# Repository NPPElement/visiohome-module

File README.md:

# visiohome-module

Open Source Hardware VHM ESP32 development board designed with KiCAD, with additional LiPo charger and battery.

## License
* Hardware is released under Apache 2.0 License
* Software is released under GPL3 License

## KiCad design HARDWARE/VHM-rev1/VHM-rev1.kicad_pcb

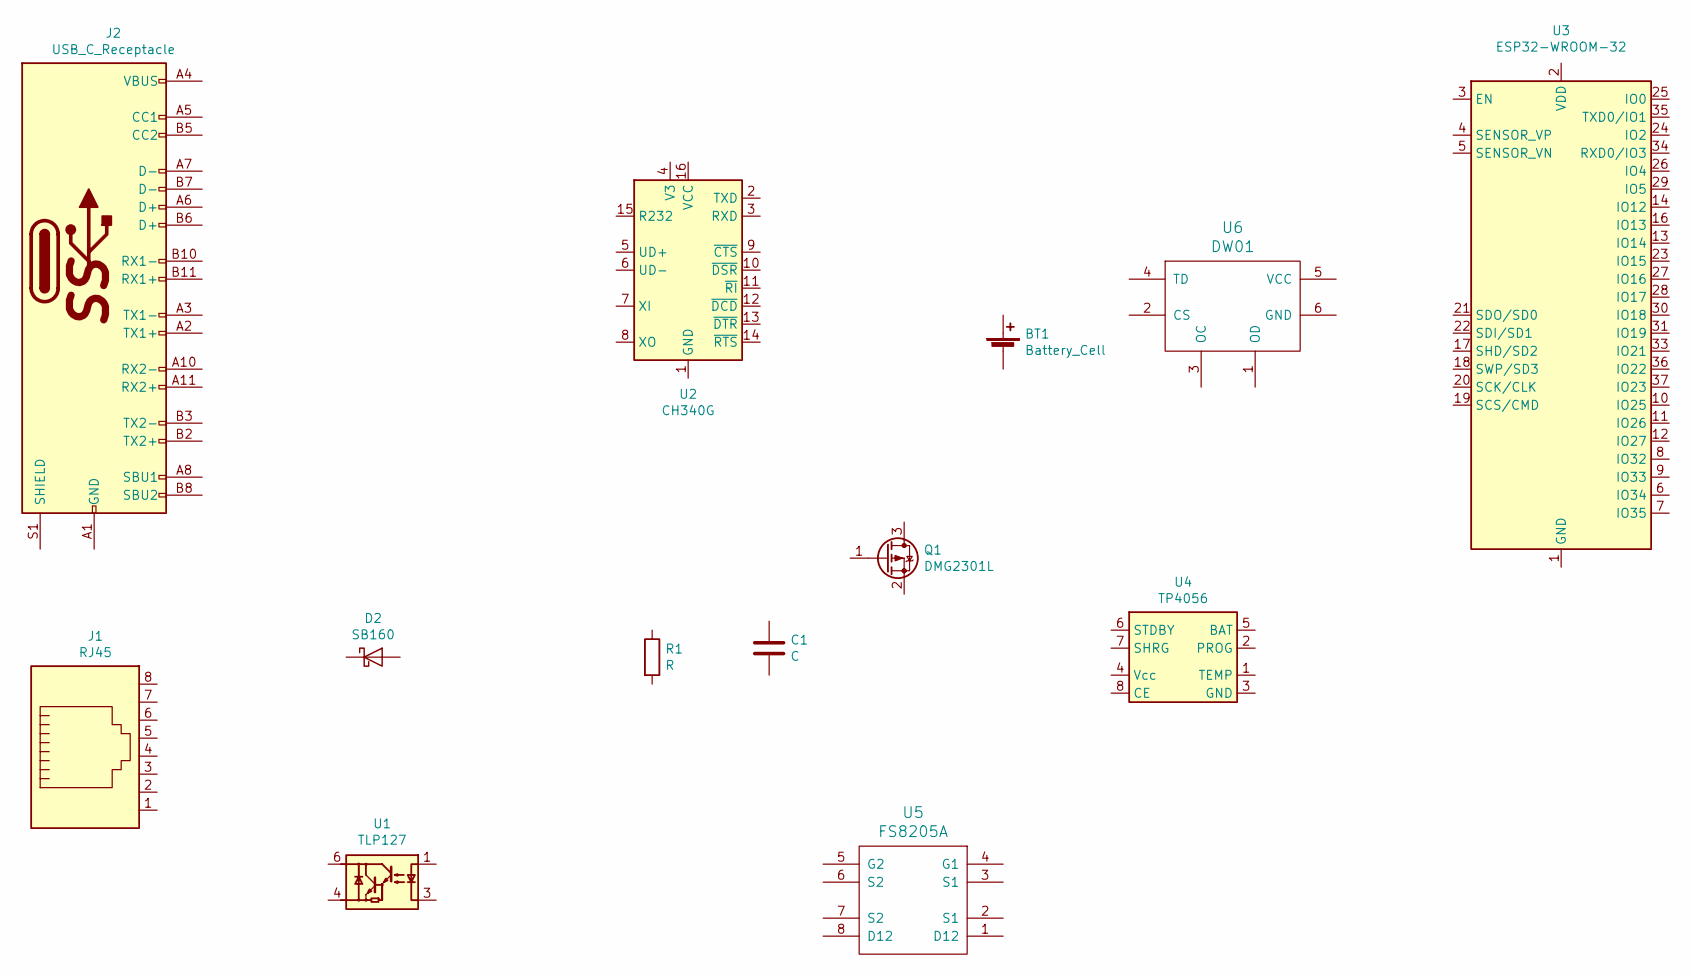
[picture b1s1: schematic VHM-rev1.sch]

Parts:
BT1: Battery_Cell; Keystone_1042_1x18650
C1: C; C_0603
D2: SB160; D_SMA
J1: RJ45; RJ45_8
J2: USB_C_Receptacle; USB_C_Plug_Molex_105444
Q1: DMG2301L; SOT-23
R1: R; R_0603
U1: TLP127; MFSOP6-4_4.4x3.6mm_Pitch1.27mm
U2: CH340G; SO-16-N
U3: ESP32-WROOM-32; ESP32-WROOM
U4: TP4056; TP4056_SOP-8-PP
U5: FS8205A; TSSOP-8_4.4x3mm_Pitch0.65mm
U6: DW01; SOT-23-6_Handsoldering

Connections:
unnamed: J2.A1 (GND), J2.A12 (GND), J2.B1 (GND), J2.B12 (GND)
unnamed: J2.A4 (VBUS), J2.A9 (VBUS), J2.B4 (VBUS), J2.B9 (VBUS)
unnamed: U3.1 (GND), U3.15 (GND), U3.38 (GND)

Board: 2 copper layers, 13 parts (2 on the bottom side), 3 nets, no tracks yet.

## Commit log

2019-11-28 Selection of components and 3D models
2019-11-28 del .DS_Store
2019-12-02 Added 3d objects and libraries
